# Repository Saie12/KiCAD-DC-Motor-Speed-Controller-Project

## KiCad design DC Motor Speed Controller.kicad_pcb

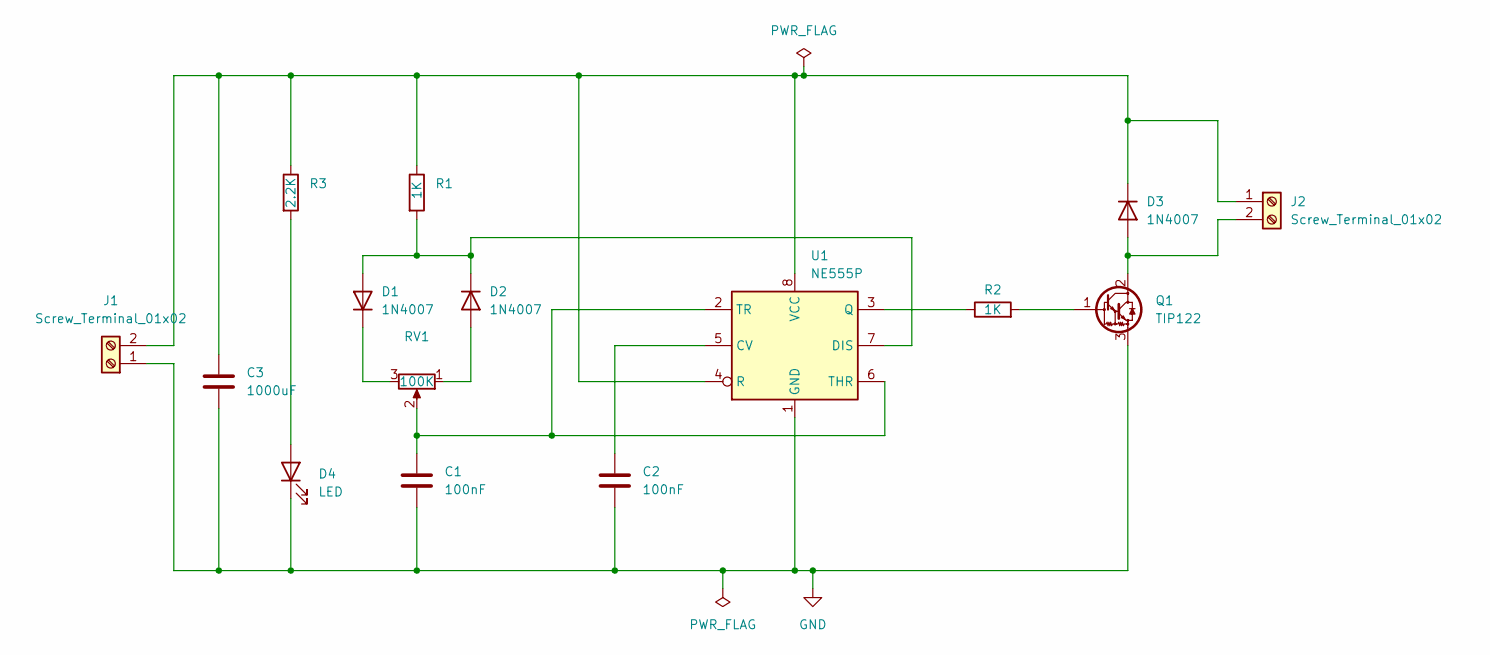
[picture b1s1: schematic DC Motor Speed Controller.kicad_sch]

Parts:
C1, C2: 100nF; C_Disc_D4.7mm_W2.5mm_P5.00mm
C3: 1000uF; C_Radial_D8.0mm_H7.0mm_P3.50mm
D1, D2, D3: 1N4007; D_DO-41_SOD81_P10.16mm_Horizontal
D4: LED; LED_D5.0mm
J1, J2: Screw_Terminal_01x02; TerminalBlock_bornier-2_P5.08mm
Q1: TIP122; TO-220-3_Vertical
R1, R2: 1K; R_Axial_DIN0204_L3.6mm_D1.6mm_P7.62mm_Horizontal
R3: 2.2K; R_Axial_DIN0204_L3.6mm_D1.6mm_P7.62mm_Horizontal
RV1: 100K; Potentiometer_Alps_RK163_Single_Horizontal
U1: NE555P; DIP-8_W7.62mm

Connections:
GND: C1.2, C2.2, C3.2, D4.1 (K), J1.1, Q1.3 (E), U1.1 (GND)
unnamed: D1.2 (A), D2.1 (K), R1.2, U1.7 (DIS)
unnamed: D1.1 (K), RV1.3
unnamed: D2.2 (A), RV1.1
unnamed: D3.2 (A), J2.2, Q1.2 (C)
unnamed: C3.1, D3.1 (K), J1.2, J2.1, R1.1, R3.1, U1.4 (R), U1.8 (VCC)
unnamed: D4.2 (A), R3.2
unnamed: Q1.1 (B), R2.2
unnamed: C2.1, U1.5 (CV)
unnamed: R2.1, U1.3 (Q)
unnamed: C1.1, RV1.2, U1.2 (TR), U1.6 (THR)

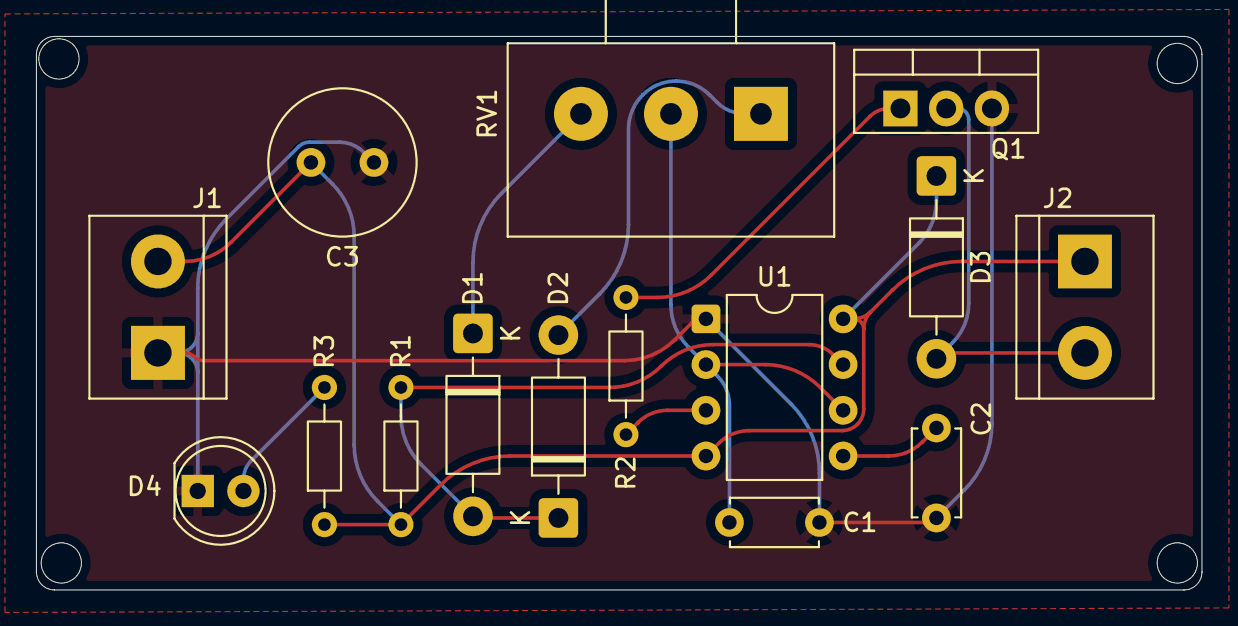
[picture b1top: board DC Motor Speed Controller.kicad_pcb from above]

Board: 2 copper layers, 64.8 x 30.8 mm, 15 parts (0 on the bottom side), 11 nets.

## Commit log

2025-07-03 Added all the components to Schematic Editor
2025-07-03 Added the Transistor_BJT component
2025-07-04 Moved components to place
2025-07-04 Moved All the Components to Place
2025-07-04 Wired some Components
2025-07-05 Connected all the components with Wires
2025-07-05 Values to Components
2025-07-05 Added GND and PWR
2025-07-05 Assigned Footprints to Components
2025-07-05 Assigned the Error footprint
2025-07-05 Schematic without ERC error
2025-07-05 Updated the Potentiometer Footprint
2025-07-05 Added Footprints to PCB Editor
2025-07-05 Placed the Footprints at Place
2025-07-05 Added Edge Cuts to PCB
2025-07-05 Added Tracks to PCB
2025-07-05 Added Round Tracks to PCB
2025-07-05 Added 3D Model Folder and Potentiometer
2025-07-05 Assigned the 3D models to all capacitors
2025-07-05 Assigned the 3D models to all Resistors
2025-07-05 Assigned the 3D model of Transistor Q1
2025-07-05 Assigned the 3D model to all the Diodes
2025-07-05 Assigned the 3D model of LED
2025-07-05 Assigned the 3D model of Timer IC (U1)
2025-07-05 Assigned the 3D model of terminal Block
2025-07-05 Completed PCB -- Remaining Datasheets to Add
